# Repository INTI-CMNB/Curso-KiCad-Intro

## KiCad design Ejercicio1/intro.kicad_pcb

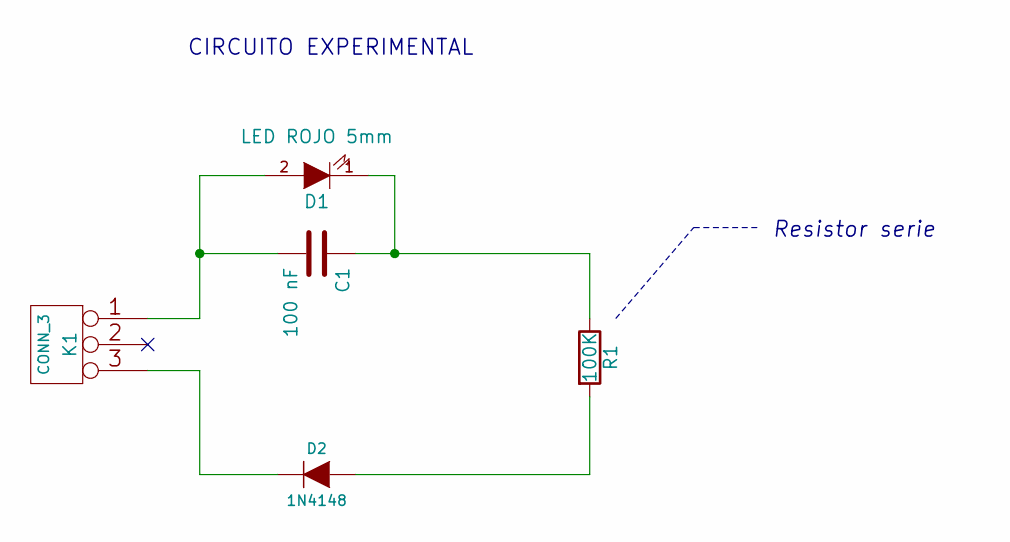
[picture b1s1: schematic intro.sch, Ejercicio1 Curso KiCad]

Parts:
C1: 100 nF; C_Rect_L7.0mm_W3.5mm_P5.00mm
D1: LED ROJO 5mm; LED_D3.0mm
D2: 1N4148; D_DO-35_SOD27_P10.16mm_Horizontal
K1: CONN_3; bornier3
R1: 100K; R_Axial_DIN0204_L3.6mm_D1.6mm_P7.62mm_Horizontal

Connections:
unnamed: C1.1, D1.1 (K), R1.1
unnamed: C1.2, D1.2 (A), K1.1
unnamed: D2.1 (K), K1.3
unnamed: D2.2 (A), R1.2

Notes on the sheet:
CIRCUITO EXPERIMENTAL
Resistor serie

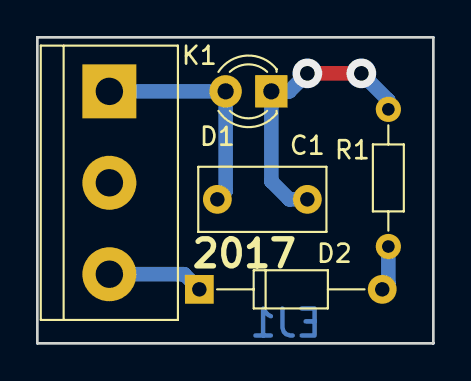
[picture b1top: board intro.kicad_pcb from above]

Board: 2 copper layers, 22.0 x 17.0 mm, 5 parts (0 on the bottom side), 4 nets.

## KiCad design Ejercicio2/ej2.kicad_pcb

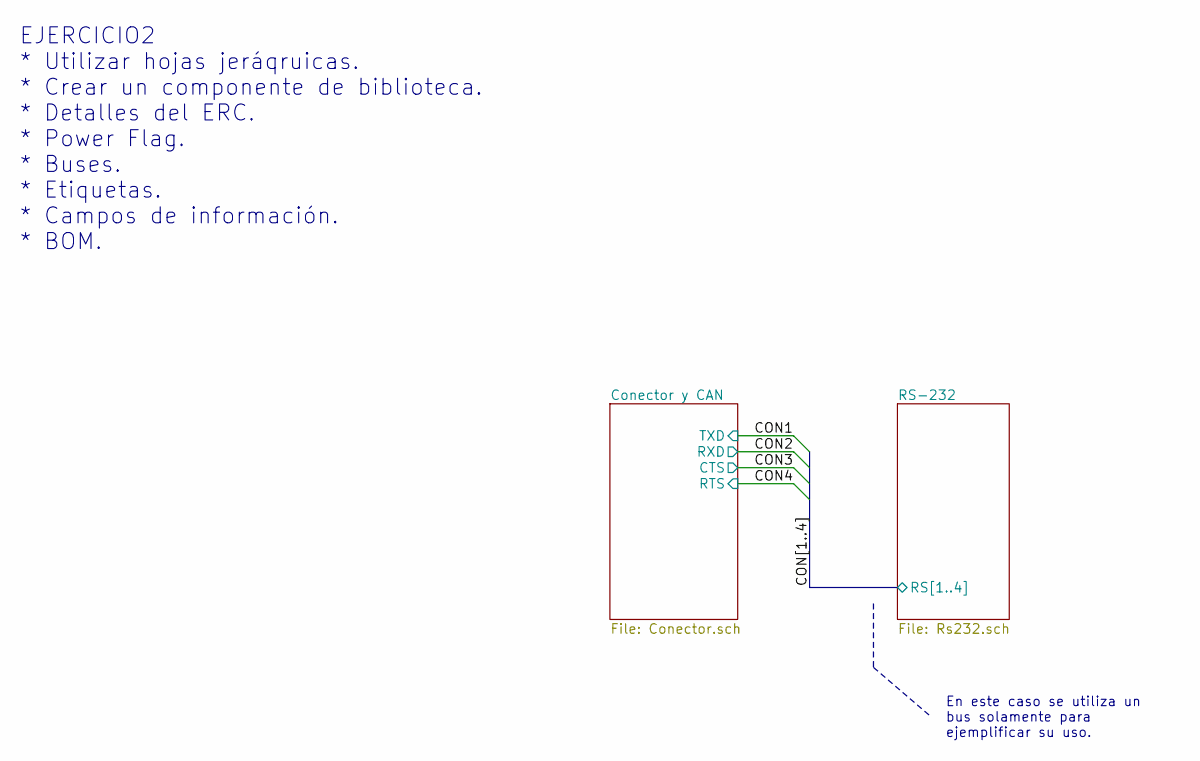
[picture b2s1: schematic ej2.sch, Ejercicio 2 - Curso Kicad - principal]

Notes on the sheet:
EJERCICIO2 * Utilizar hojas jeráqruicas. * Crear un componente de biblioteca. * Detalles del ERC. * Power Flag. * Buses. * Etiquetas. * Campos de información. * BOM.
En este caso se utiliza un bus solamente para ejemplificar su uso.

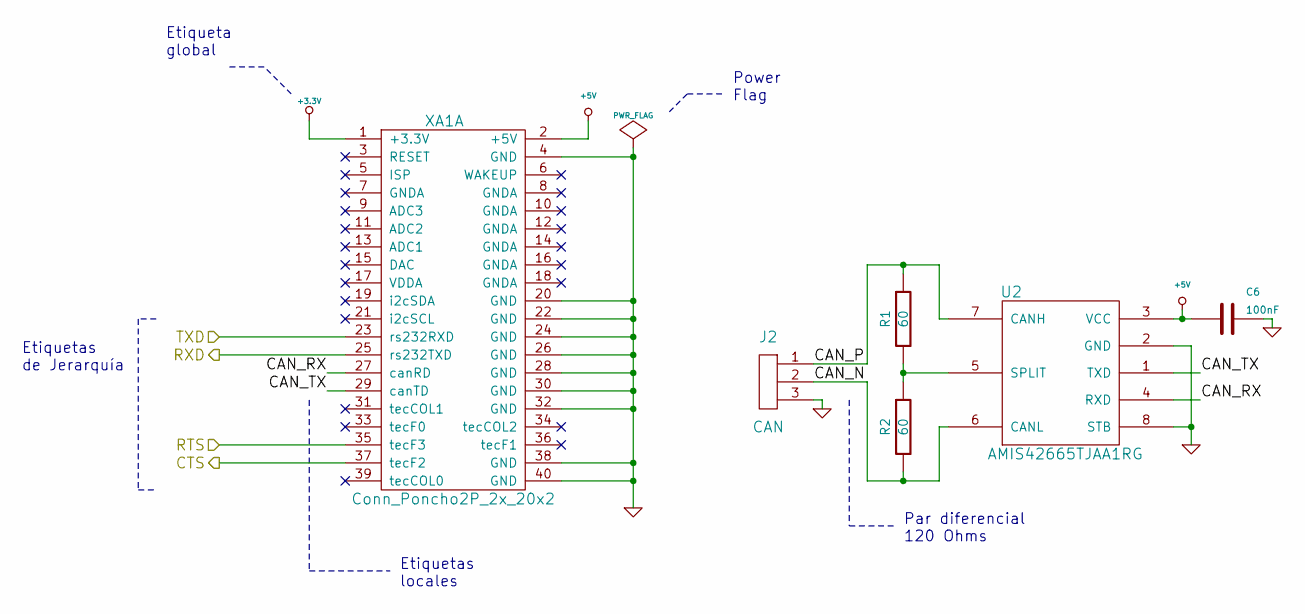
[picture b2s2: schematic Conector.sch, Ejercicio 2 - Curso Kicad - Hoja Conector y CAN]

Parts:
C6: 100nF; C_1206_HandSoldering; Digikey/Mouser 311-1179-1-ND
J2: CAN; CON_PALETA_3; Digikey/Mouser A19470-ND
R1, R2: 60; R_1206_HandSoldering; Digikey/Mouser Y149660R0000A0R-ND
U2: AMIS42665TJAA1RG; SOIC-8; Digikey/Mouser 766-1006-1-ND
XA1: Conn_Poncho2P_2x_20x2; Conn_Poncho_Derecha; Digikey/Mouser 952-1387-ND

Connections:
+3.3V: XA1.1 (+3.3V); also elsewhere on the board
+5V: C6.2, U2.3 (VCC), XA1.2 (+5V)
/Conector y CAN/CAN_N: J2.2, R2.2, U2.6 (CANL)
/Conector y CAN/CAN_P: J2.1, R1.1, U2.7 (CANH)
/Conector y CAN/CAN_RX: U2.4 (RXD), XA1.27 (canRD)
/Conector y CAN/CAN_TX: U2.1 (TXD), XA1.29 (canTD)
/Conector y CAN/CTS: XA1.37 (tecF2); also elsewhere on the board
/Conector y CAN/RTS: XA1.35 (tecF3); also elsewhere on the board
/Conector y CAN/RXD: XA1.25 (rs232TXD); also elsewhere on the board
/Conector y CAN/TXD: XA1.23 (rs232RXD); also elsewhere on the board
GND: C6.1, J2.3, U2.2 (GND), U2.8 (STB), XA1.4 (GND), XA1.20 (GND), XA1.22 (GND), XA1.24 (GND), XA1.26 (GND), XA1.28 (GND), XA1.30 (GND), XA1.32 (GND), XA1.38 (GND), XA1.40 (GND); also elsewhere on the board
unnamed: R1.2, R2.1, U2.5 (SPLIT)

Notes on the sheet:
Etiquetas de Jerarquía
Etiqueta global
Power Flag
Etiquetas locales
Par diferencial 120 Ohms

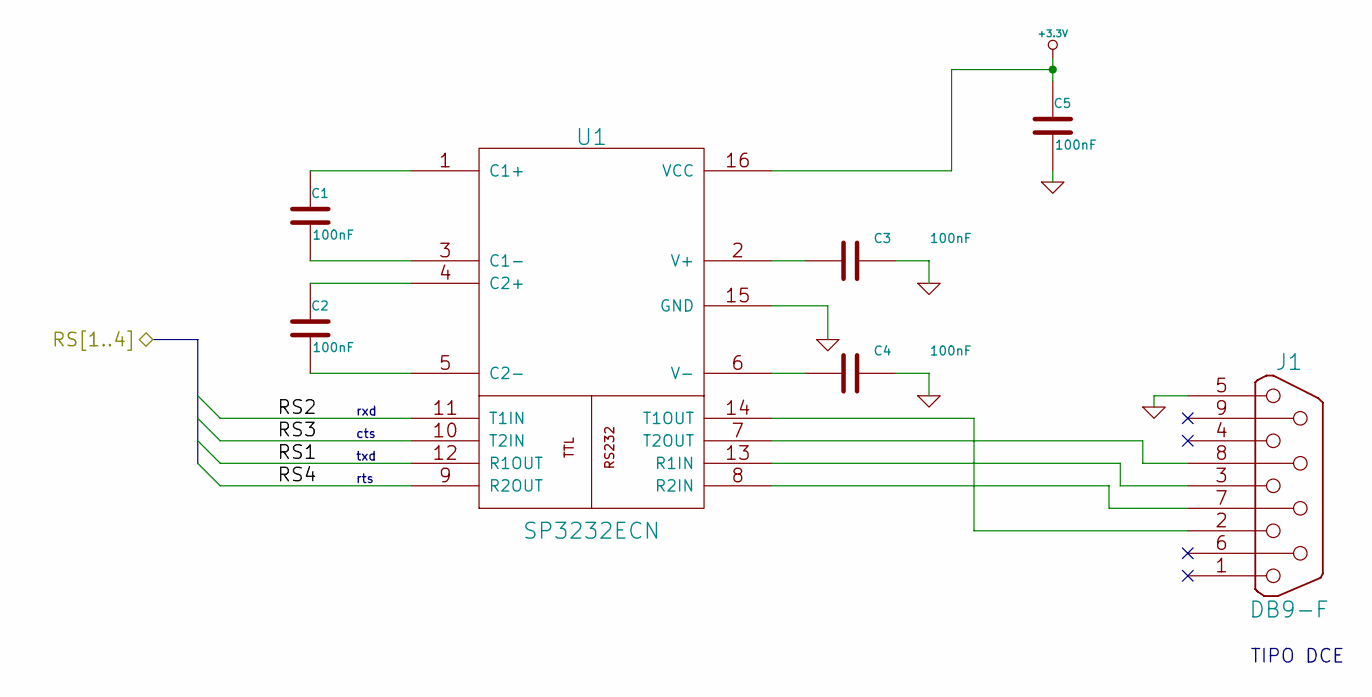
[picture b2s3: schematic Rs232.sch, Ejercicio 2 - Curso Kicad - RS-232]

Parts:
C1, C2, C3, C4, C5: 100nF; C_1206_HandSoldering; Digikey/Mouser 311-1179-1-ND
J1: DB9-F; DB9_F_TH; Digikey/Mouser S9554-ND
U1: SP3232ECN; SP3232ECN-SOIC16N; Digikey/Mouser 1016-1803-1-ND

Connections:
+3.3V: C5.1, U1.16 (VCC); also elsewhere on the board
/Conector y CAN/CTS: U1.10 (T2IN); also elsewhere on the board
/Conector y CAN/RTS: U1.9 (R2OUT); also elsewhere on the board
/Conector y CAN/RXD: U1.11 (T1IN); also elsewhere on the board
/Conector y CAN/TXD: U1.12 (R1OUT); also elsewhere on the board
GND: C3.1, C4.1, C5.2, J1.5, U1.15 (GND); also elsewhere on the board
unnamed: C1.1, U1.1 (C1+)
unnamed: C1.2, U1.3 (C1-)
unnamed: C2.1, U1.4 (C2+)
unnamed: C2.2, U1.5 (C2-)
unnamed: C3.2, U1.2 (V+)
unnamed: C4.2, U1.6 (V-)
unnamed: J1.2, U1.14 (T1OUT)
unnamed: J1.3, U1.13 (R1IN)
unnamed: J1.7, U1.8 (R2IN)
unnamed: J1.8, U1.7 (T2OUT)

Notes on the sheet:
TIPO DCE
rxd
txd
cts
rts

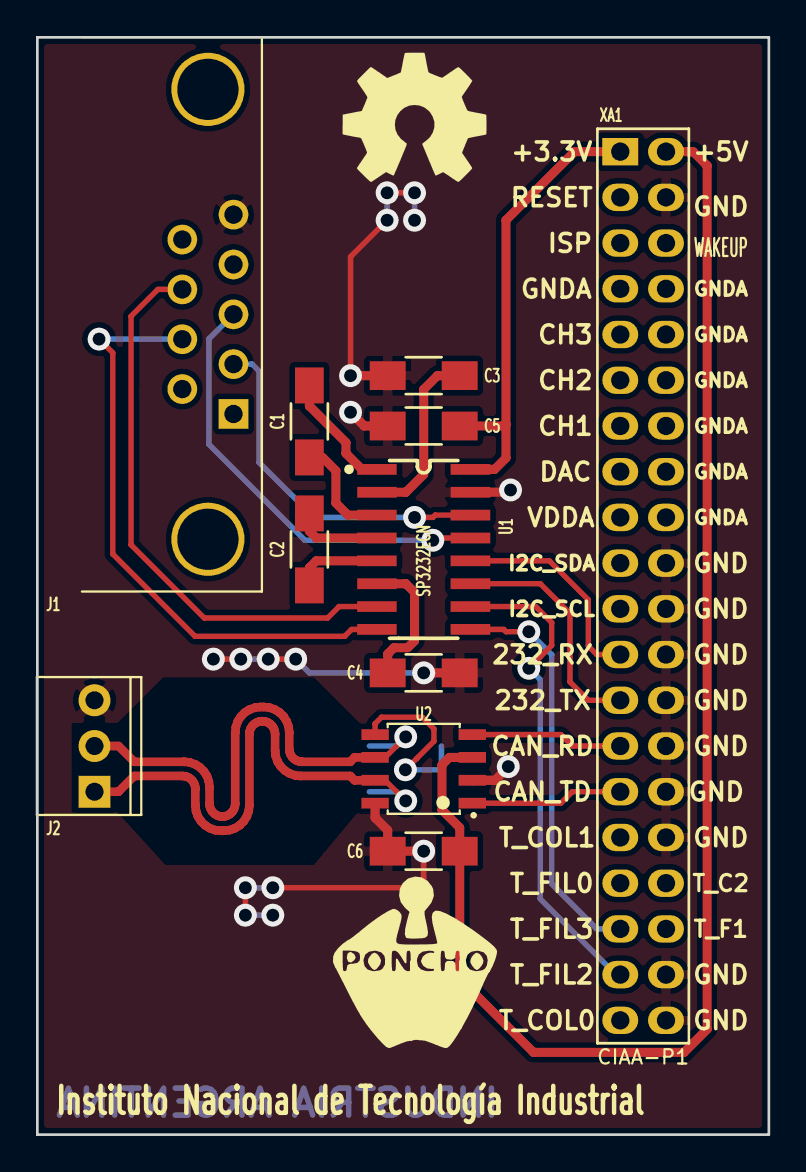
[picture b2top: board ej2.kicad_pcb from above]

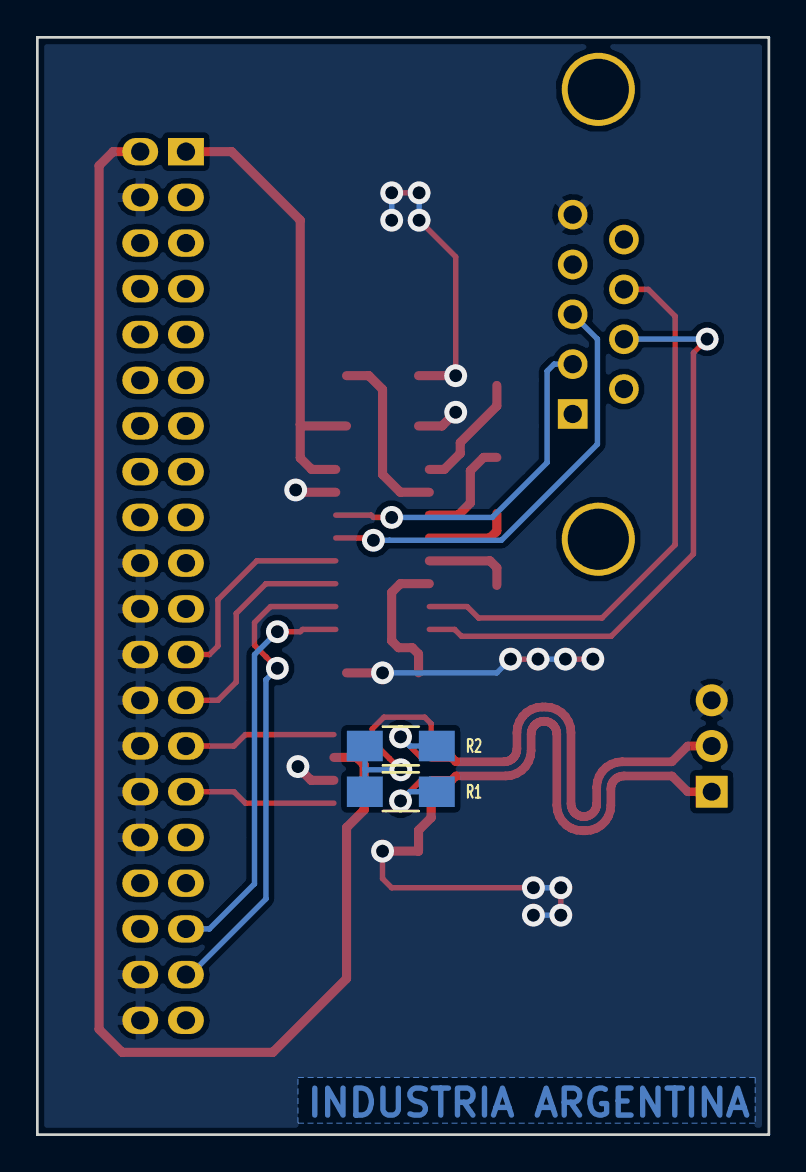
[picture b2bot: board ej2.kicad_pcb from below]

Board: 2 copper layers, 40.6 x 61.0 mm, 15 parts (2 on the bottom side), 22 nets.

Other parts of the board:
G101: Logo_OSHWA
G102: LOGO; Logo_Poncho

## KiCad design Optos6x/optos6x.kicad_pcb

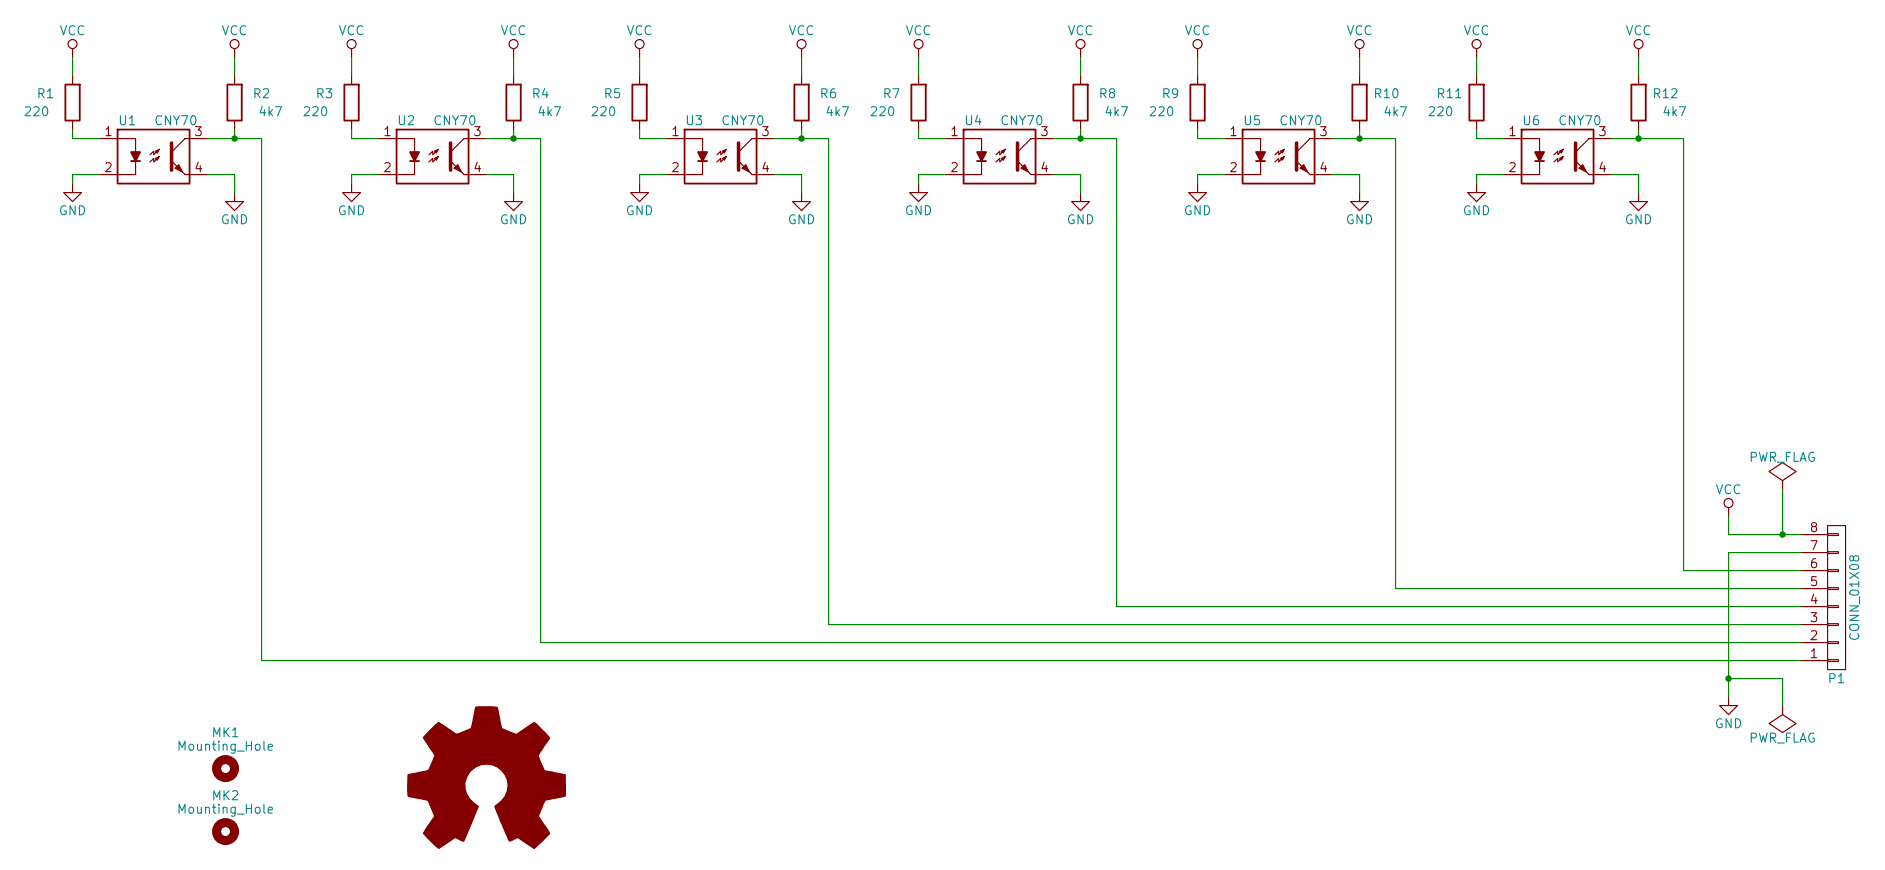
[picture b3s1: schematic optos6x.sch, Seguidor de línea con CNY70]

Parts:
LOGO1: Logo_Open_Hardware_Large; OSHW-Logo2_7.3x6mm_SilkScreen
MK1, MK2: Mounting_Hole; MountingHole_2.2mm_M2_DIN965_Pad
P1: CONN_01X08; Pin_Header_Straight_1x08_Pitch2.54mm
R1, R3, R5, R7, R9, R11: 220; R_Axial_DIN0207_L6.3mm_D2.5mm_P7.62mm_Horizontal
R2, R4, R6, R8, R10, R12: 4k7; R_Axial_DIN0207_L6.3mm_D2.5mm_P7.62mm_Horizontal
U1, U2, U3, U4, U5, U6: CNY70

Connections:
GND: P1.7, U1.2, U1.4, U2.2, U2.4, U3.2, U3.4, U4.2, U4.4, U5.2, U5.4, U6.2, U6.4
unnamed: P1.1, R2.1, U1.3
unnamed: P1.2, R4.1, U2.3
unnamed: P1.3, R6.1, U3.3
unnamed: P1.4, R8.1, U4.3
unnamed: P1.5, R10.1, U5.3
unnamed: P1.6, R12.1, U6.3
unnamed: R1.1, U1.1
unnamed: R3.1, U2.1
unnamed: R5.1, U3.1
unnamed: R7.1, U4.1
unnamed: R9.1, U5.1
unnamed: R11.1, U6.1
VCC: P1.8, R1.2, R2.2, R3.2, R4.2, R5.2, R6.2, R7.2, R8.2, R9.2, R10.2, R11.2, R12.2

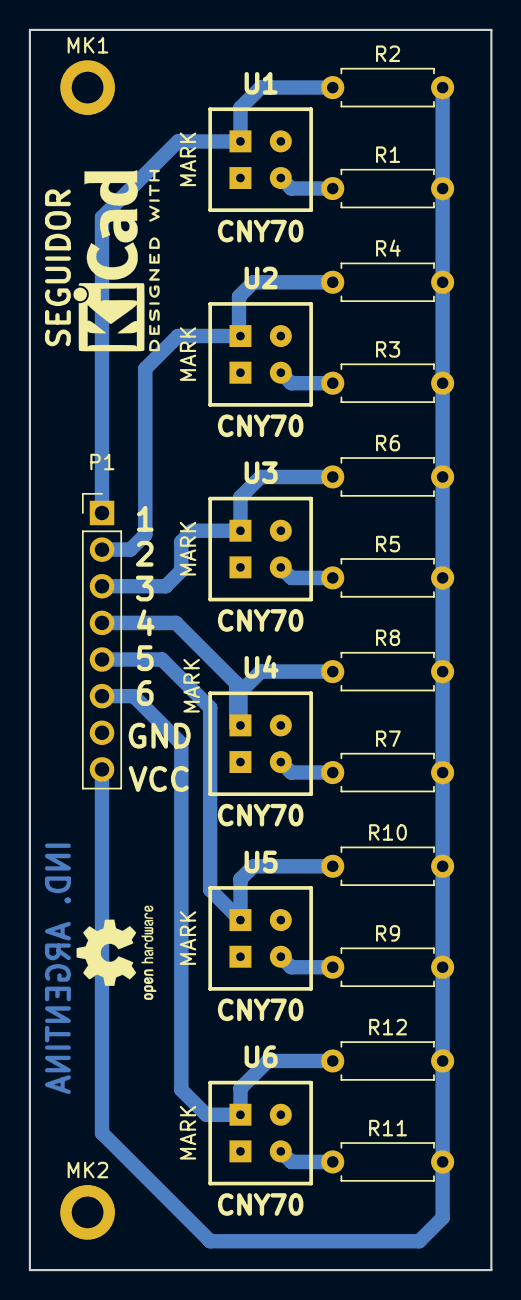
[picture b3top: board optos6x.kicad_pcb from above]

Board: 2 copper layers, 32.0 x 86.0 mm, 22 parts (0 on the bottom side), 14 nets.

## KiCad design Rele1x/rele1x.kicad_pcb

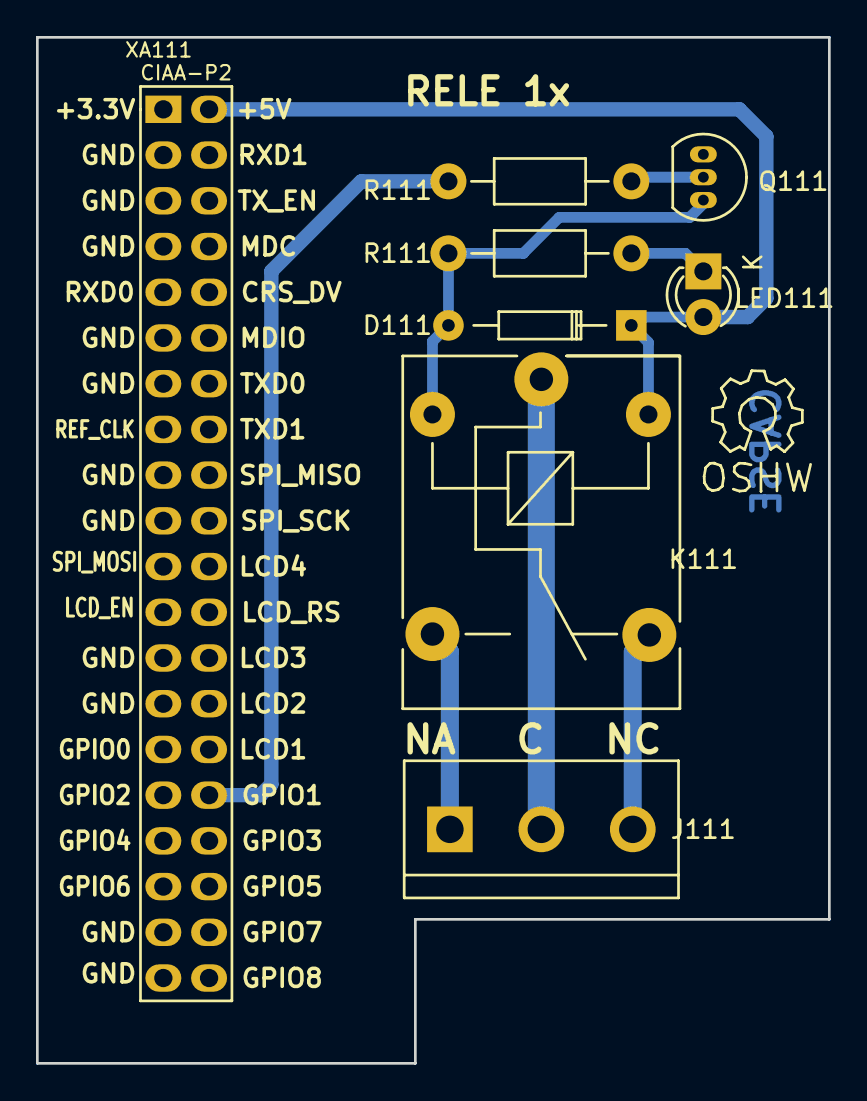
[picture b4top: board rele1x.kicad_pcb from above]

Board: 2 copper layers, 44.0 x 57.0 mm, 8 parts (0 on the bottom side), 9 nets.

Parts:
D111: 1N4148; Diode_DO-35_SOD27_Horizontal_RM10
J111: TB_1X3; bornier3
K111: RELAY_C; Relay_SANYOU_SRD_Series_Form_C
LED111: LED; LED-3MM
Q111: 2N3904; TO-92_Inline_Narrow_Oval
R111: 2K7; Resistor_Horizontal_RM10mm
R111#2: 330R; Resistor_Horizontal_RM10mm
XA111: Conn_Poncho2P_2x_20x2; Conn_Poncho_Izquierdo

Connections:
+5VP: D111.1, K111.5, LED111.2, XA111.42
GNDD: Q111.1, XA111.43, XA111.45, XA111.47, XA111.51, XA111.53, XA111.57, XA111.59, XA111.65, XA111.67, XA111.77, XA111.79
unnamed: D111.2, K111.2, Q111.3, R111#2.2
unnamed: J111.1, K111.3
unnamed: J111.2, K111.1
unnamed: J111.3, K111.4
unnamed: LED111.1, R111#2.1
unnamed: Q111.2, R111.1
unnamed: R111.2, XA111.72

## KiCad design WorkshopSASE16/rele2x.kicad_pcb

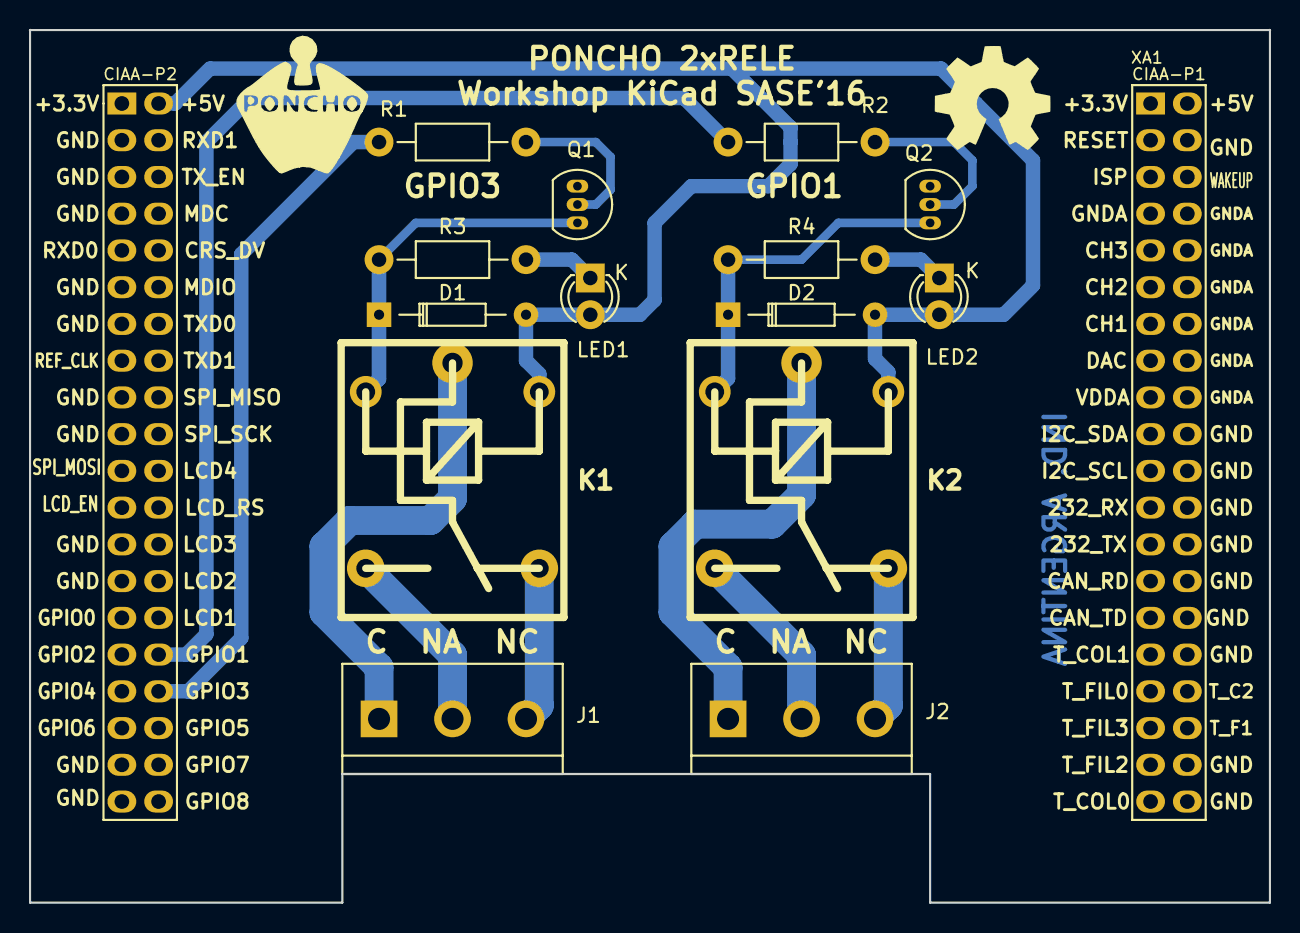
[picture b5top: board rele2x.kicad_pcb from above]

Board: 2 copper layers, 85.7 x 60.3 mm, 16 parts (0 on the bottom side), 16 nets.

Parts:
D1, D2: 1N4148; Diode_DO-35_SOD27_Horizontal_RM10
G101: Logo_OSHWA
J1, J2: TB_1X3; bornier3
K1, K2: RELAY_C; Relay_C
LED1, LED2: LED; LED-3MM
Q1, Q2: 2N3904; TO-92_Inline_Narrow_Oval
R1, R2: 2K7; Resistor_Horizontal_RM10mm
R3, R4: 330R; Resistor_Horizontal_RM10mm
XA1: Conn_Poncho2P_2x_20x2; Conn_Poncho_SinBorde

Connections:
+5VP: D1.2, D2.2, K1.5, K2.5, LED1.2, LED2.2, XA1.42
GND: Q1.1, Q2.1, XA1.4, XA1.20, XA1.22, XA1.24, XA1.26, XA1.28, XA1.30, XA1.32, XA1.38, XA1.40, XA1.43, XA1.45, XA1.47, XA1.51, XA1.53, XA1.57, XA1.59, XA1.65, XA1.67, XA1.77, XA1.79
unnamed: D1.1, K1.2, Q1.3, R3.2
unnamed: D2.1, K2.2, Q2.3, R4.2
unnamed: J1.1, K1.1
unnamed: J1.2, K1.3
unnamed: J1.3, K1.4
unnamed: J2.1, K2.1
unnamed: J2.2, K2.3
unnamed: J2.3, K2.4
unnamed: LED1.1, R3.1
unnamed: LED2.1, R4.1
unnamed: Q1.2, R1.1
unnamed: Q2.2, R2.1
unnamed: R1.2, XA1.74
unnamed: R2.2, XA1.72
